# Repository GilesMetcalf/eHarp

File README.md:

# Lughnasadh eHarp
This is the ongoing eHarp project. 

## feature summary
The eharp is a full-featured MIDI controller that offers the following functions:
- Up to 32 notes that can be played
- Fully polyphonic
- A choice of 32 different scales (modes)
- A choice of MIDI channels
- Transposition from -6 to +6 intervals. Essentially any key in the octave.
- Selectable octave settings from -3 to +3
- 11 selectable velocity settings
- Pitch and Bend controls
- Sustain pedal input
- Multi-level menu system
- Save and Load up to 8 sets of parameters ("songs")
- Self-calibration to compensate for background light levels
- Several self-diagnostic features

## Architecture and principles
The eHarp is based on a scanned matrix of small lasers to detect an interruption to the beam (by sticking fingers into the beam!). The interruption is detected by a phototransistor which feeds an baseline-compensated analogue level amplifier and a digital comparator. A microcontroller (a Raspberry Pi Pico 2) runs CircuitPython code to detect the interruption, identify which laser is on at the time, makes appropriate adjustments depending on the selected scale, velocity, bend value and transposition, and them emits MIDI messages to whatever device is on the end. 

The lasers are small 5mW diodes (such as are used in laser pointers), scanned sequentially by the microcontroller. Only "active" diodes are scanned, so any which are not part of the scale, or that have been identified as blocked or faulty by the calibration routines are not illuminated and are skipped from the scan. This reduces any latency in generating notes, as well as preventing spurious notes playing.

## Boot and run sequences
### Boot up and calibration
On initially powering the eHarp up, the (numerous) I/O ports are initialised and the baseline offset output set to a default value of approximately 150mV. A flag is set to prevent any MIDI output (this stops random notes playing during calibration). A nice splash screen is displayed for a few seconds. This serves no purpose other than being flash, and can be aborted by pressing any button on the menu panel. The software twiddles it's little digital thumbs while this is displayed.
Once the splash expires, the eHarp drops into it's automated calibration routine. There are two elements to this. Firstly the baseline offset is adjusted to allow for the current ambient light by reading the sensor output (post amplification) with no lasers on. The offset voltage is adjusted to approximately 30-50mV above zero to give a bit of stability. 
Following the offset adjustment, all the lasers are scanned to check that they are producing an output and that the sensor is detecting them. (This assumes that there are no fingers in the way for this part!) Any which fail for any reason (poor and failing output - always a danger with cheap laser diodes! - misalignments or blockages, etc.) are marked as inactive and removed from normal scans. 
Finally, the main menu is displayed and the main scan routines are initiated.

### Run cycle
The run cycle essentially runs forever, and consists of three elements:
- The menu buttons are scanned. If any have been pressed, the menu subsystem executes whatever menu option is selected. This might be to change to a submenu, reset a state value (such as scale or key), or execute a calibration or diagnostic function. Once the action has been carried out, the menu returns to the parent level (or the main level, depending where it is in the heirarchy), and normal scanning continues.
- The laser matrix is scanned. All the available cells (0 to 31) are processed in sequence, and for each cell if the selected scale array and active note array both indicate that the cell is valid, the laser is illuminated. The sensor input is read, and if the beam is interrupted the current MIDI state for that note is checked. There are several possible outcomes at this stage:
  - The beam is not interrupted and the note is not active; do nothing and move on to the next cell.
  - The beam is not interrupted but the note was active; emit a <samp>NoteOff</samp> MIDI message.
  - The beam is interrupted and the note was active; do nothing and move on to the next cell.
  - The beam is interrupted and the note was not active; emit a <samp>NoteOn</samp> MIDI message.
- Once the cell has been  processed, the laser is turned off and the sequence moves to the next cell.
- Finally, once all the cells have been processed, the MIDI state (bend/mod controls and octave selection buttons) are scanned. Any changes are detected and state variables set accordingly. The bend and mod controls are analogue inputs from a joystick and are captured using the Pico's built-in ADC.

### MIDI generation
For each MIDI note generation event, before the <samp>NoteOn</samp> event is emitted, some adjustments and enhancements are needed. The <samp>NoteOn</samp> event contains several parameters:
- The actual note number, which is calculated from the cell number (0 to 31) plus the MIDI offset to get to the actual note (C3 for the bottom note). This is then appended with the transposition value (-6 to +6) and the octave value to give the required note.
- The velocity value (how hard the 'key' has been struck). This comes from the selected velocity value
- The MIDI channel number. This comes from the selected channel value.
  
On top of that, there are some MIDI control events that also need to be emitted, although these are not directly associated with a specific note:
- If the Bend control value has changed, a <samp>PitchBend</samp> event is emitted.
- If the Mod control value has changed, a <samp>ControlChange(1)</samp> event is emitted.
- If the Sustain pedal is pressed, a <samp>ControlChange(64)</samp> event is emitted with a parameter of 127 (sustain on).
- If the Sustain pedal is released, a <samp>ControlChange(64)</samp> event is emitted with a parameter of 0 (sustain off).

### Parameter saving
The user can save and reload up to 8 sets of parameters for different songs:
- Scale
- Velocity
- MIDI channel
- Transposition
- Octave setting

*My thanks also to Adam Metcalf for the original inspiration, as well as much sage advice during the design and build of this project (and not laughing at my terrible electronics!)*

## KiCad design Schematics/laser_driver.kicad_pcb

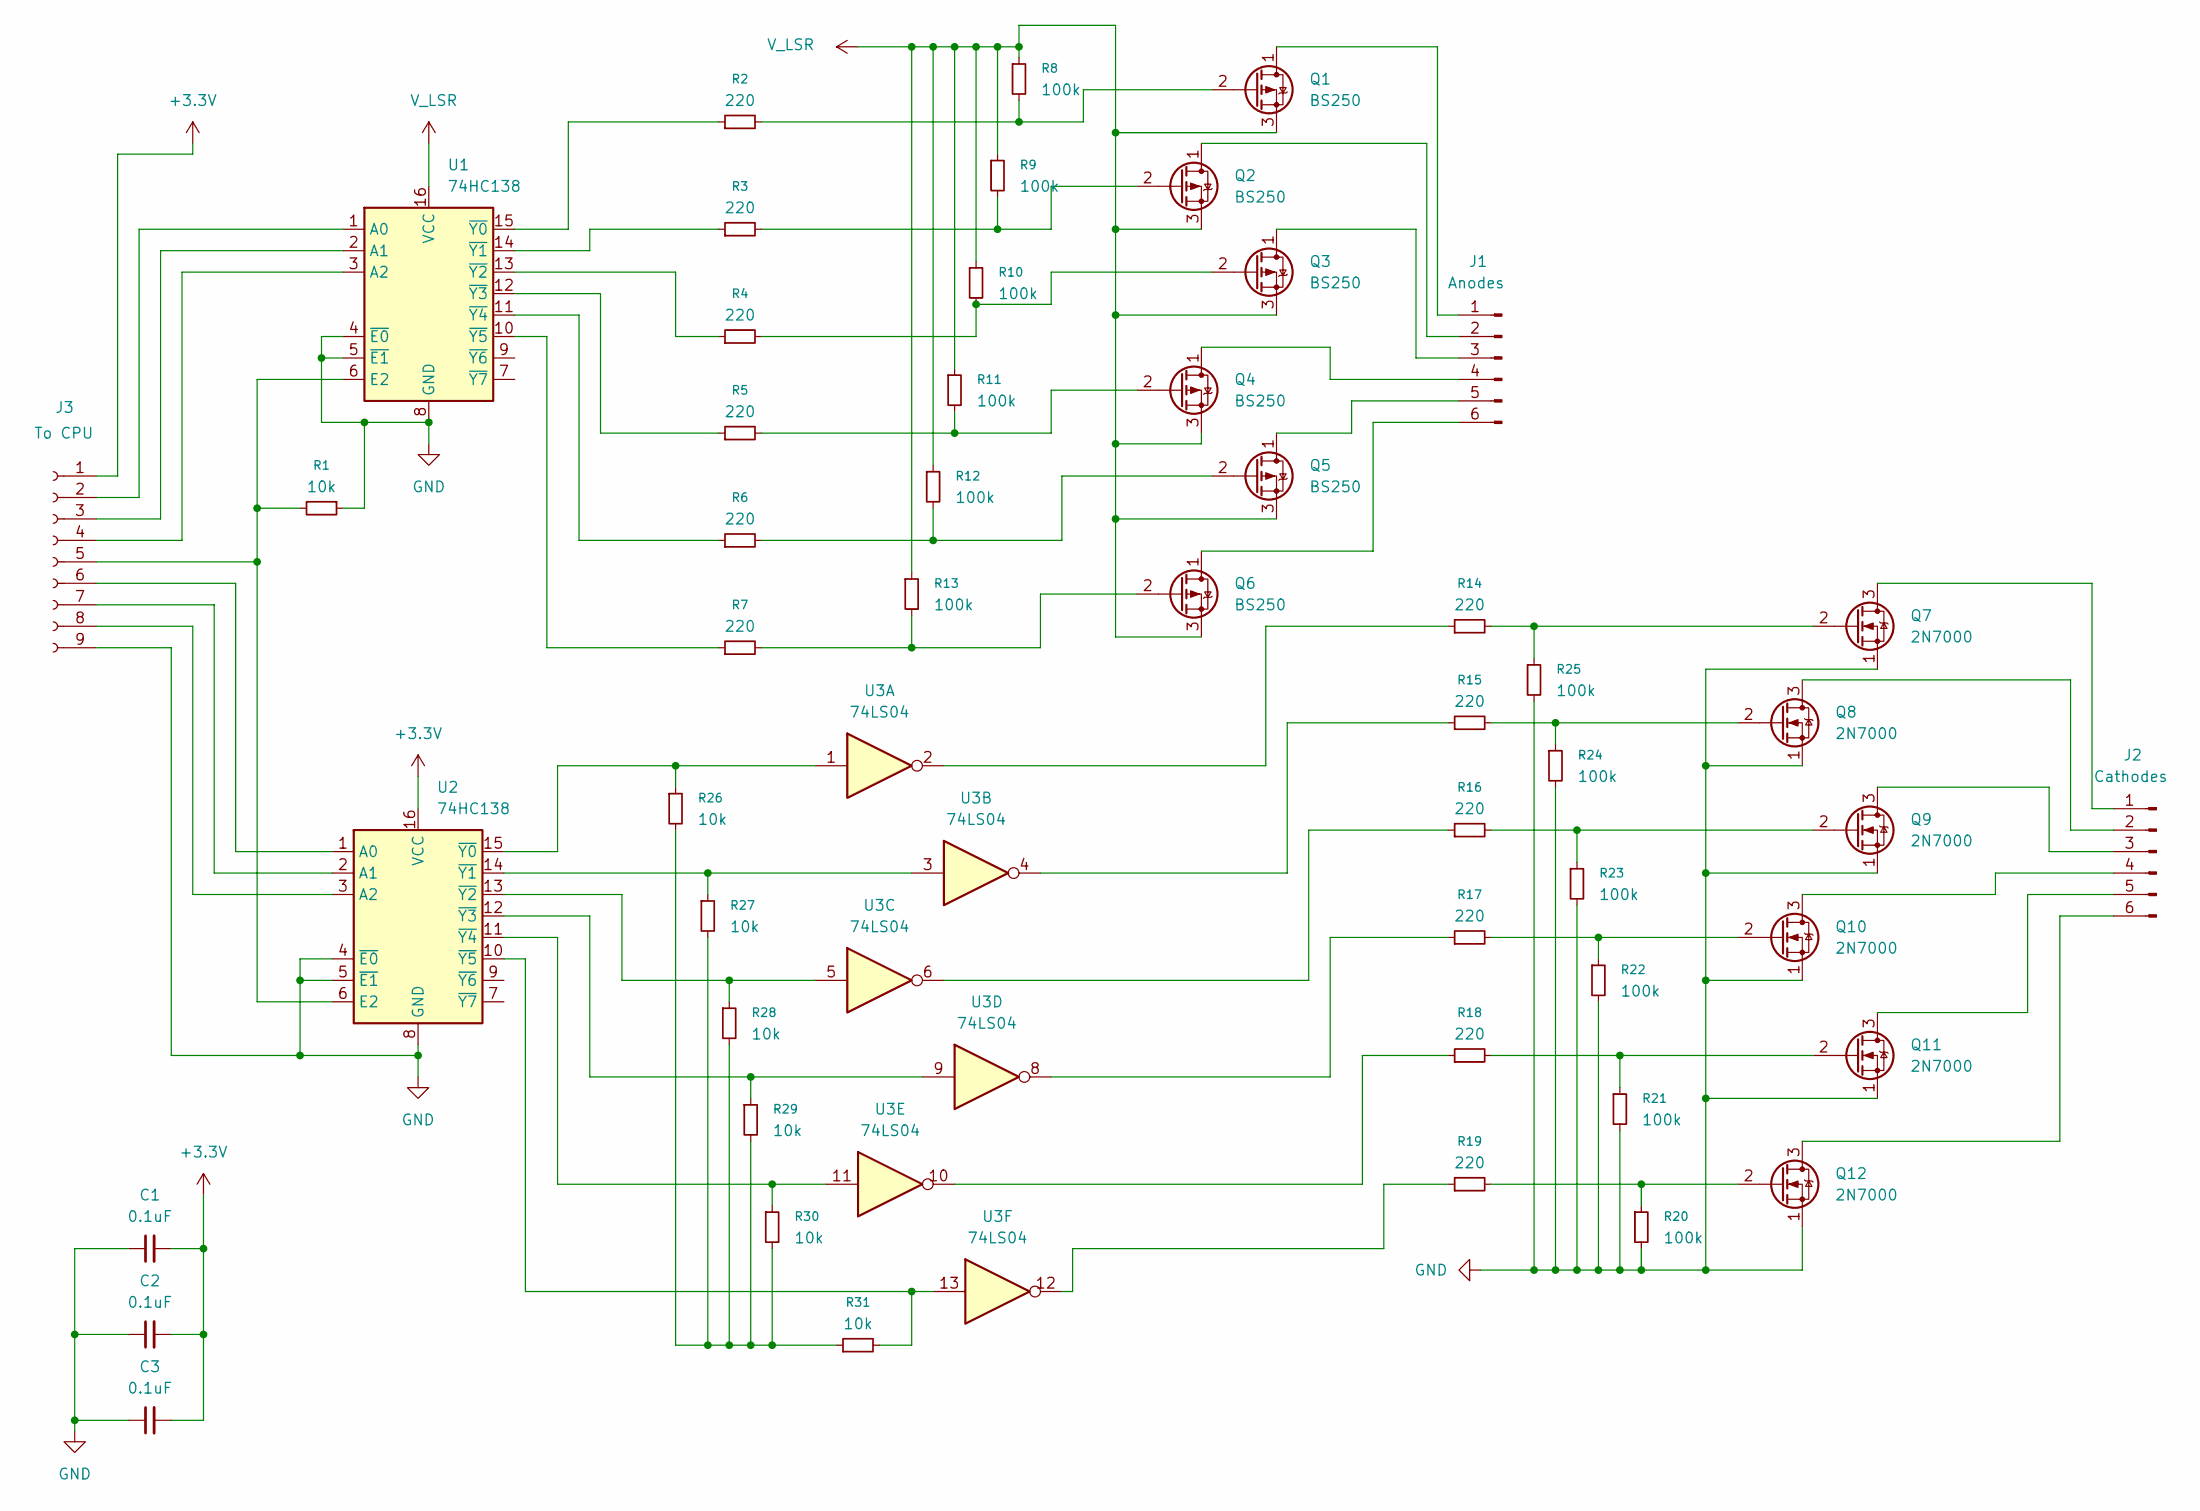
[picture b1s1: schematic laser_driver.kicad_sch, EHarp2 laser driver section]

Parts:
C1, C2, C3: 0.1uF; C_Rect_L10.0mm_W3.0mm_P7.50mm_FKS3_FKP3
J1: Anodes; PinHeader_1x06_P2.54mm_Vertical
J2: Cathodes; PinHeader_1x06_P2.54mm_Vertical
J3: To CPU; PinHeader_1x09_P2.54mm_Vertical
Q1, Q2, Q3, Q4, Q5, Q6: BS250; TO-92_Inline
Q7, Q8, Q9, Q10, Q11, Q12: 2N7000; TO-92_Inline
R1, R26, R27, R28, R29, R30, R31: 10k; R_Axial_DIN0204_L3.6mm_D1.6mm_P7.62mm_Horizontal
R2, R3, R4, R5, R6, R7, R14, R15, R16, R17, R18, R19: 220; R_Axial_DIN0204_L3.6mm_D1.6mm_P7.62mm_Horizontal
R8, R9, R10, R11, R12, R13, R20, R21, R22, R23, R24, R25: 100k; R_Axial_DIN0204_L3.6mm_D1.6mm_P7.62mm_Horizontal
U1, U2: 74HC138; DIP-16_W10.16mm
U3: 74LS04

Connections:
+3.3V: C1.2, C2.2, C3.2, J3.1, U2.16 (VCC)
GND: C1.1, C2.1, C3.1, J3.9, Q7.1 (S), Q8.1 (S), Q9.1 (S), Q10.1 (S), Q11.1 (S), Q12.1 (S), R1.1, R20.2, R21.2, R22.2, R23.2, R24.2, R25.2, U1.4 (~E0), U1.5 (~E1), U1.8 (GND), U2.4 (~E0), U2.5 (~E1), U2.8 (GND)
unnamed: J1.1, Q1.1 (D)
unnamed: J1.2, Q2.1 (D)
unnamed: J1.3, Q3.1 (D)
unnamed: J1.4, Q4.1 (D)
unnamed: J1.5, Q5.1 (D)
unnamed: J1.6, Q6.1 (D)
unnamed: J2.1, Q7.3 (D)
unnamed: J2.2, Q8.3 (D)
unnamed: J2.3, Q9.3 (D)
unnamed: J2.4, Q10.3 (D)
unnamed: J2.5, Q11.3 (D)
unnamed: J2.6, Q12.3 (D)
unnamed: J3.2, U1.1 (A0)
unnamed: J3.3, U1.2 (A1)
unnamed: J3.4, U1.3 (A2)
unnamed: J3.5, R1.2, U1.6 (E2), U2.6 (E2)
unnamed: J3.6, U2.1 (A0)
unnamed: J3.7, U2.2 (A1)
unnamed: J3.8, U2.3 (A2)
unnamed: Q1.2 (G), R2.2, R8.2
unnamed: Q2.2 (G), R3.2, R9.2
unnamed: Q3.2 (G), R4.2, R10.2
unnamed: Q4.2 (G), R5.2, R11.2
unnamed: Q5.2 (G), R6.2, R12.2
unnamed: Q6.2 (G), R7.2, R13.2
unnamed: Q7.2 (G), R14.2, R25.1
unnamed: Q8.2 (G), R15.2, R24.1
unnamed: Q9.2 (G), R16.2, R23.1
unnamed: Q10.2 (G), R17.2, R22.1
unnamed: Q11.2 (G), R18.2, R21.1
unnamed: Q12.2 (G), R19.2, R20.1
unnamed: R14.1, U3.2
unnamed: R15.1, U3.4
unnamed: R16.1, U3.6
unnamed: R17.1, U3.8
unnamed: R18.1, U3.10
unnamed: R19.1, U3.12
unnamed: R26.2, R27.2, R28.2, R29.2, R30.2, R31.1
unnamed: R2.1, U1.15 (~Y0)
unnamed: R3.1, U1.14 (~Y1)
unnamed: R4.1, U1.13 (~Y2)
unnamed: R5.1, U1.12 (~Y3)
unnamed: R6.1, U1.11 (~Y4)
unnamed: R7.1, U1.10 (~Y5)
unnamed: R26.1, U2.15 (~Y0), U3.1
unnamed: R27.1, U2.14 (~Y1), U3.3
unnamed: R28.1, U2.13 (~Y2), U3.5
unnamed: R29.1, U2.12 (~Y3), U3.9
unnamed: R30.1, U2.11 (~Y4), U3.11
unnamed: R31.2, U2.10 (~Y5), U3.13
V_LSR: Q1.3 (S), Q2.3 (S), Q3.3 (S), Q4.3 (S), Q5.3 (S), Q6.3 (S), R8.1, R9.1, R10.1, R11.1, R12.1, R13.1, U1.16 (VCC)

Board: 2 copper layers, 52 parts (0 on the bottom side), 53 nets, no tracks yet.

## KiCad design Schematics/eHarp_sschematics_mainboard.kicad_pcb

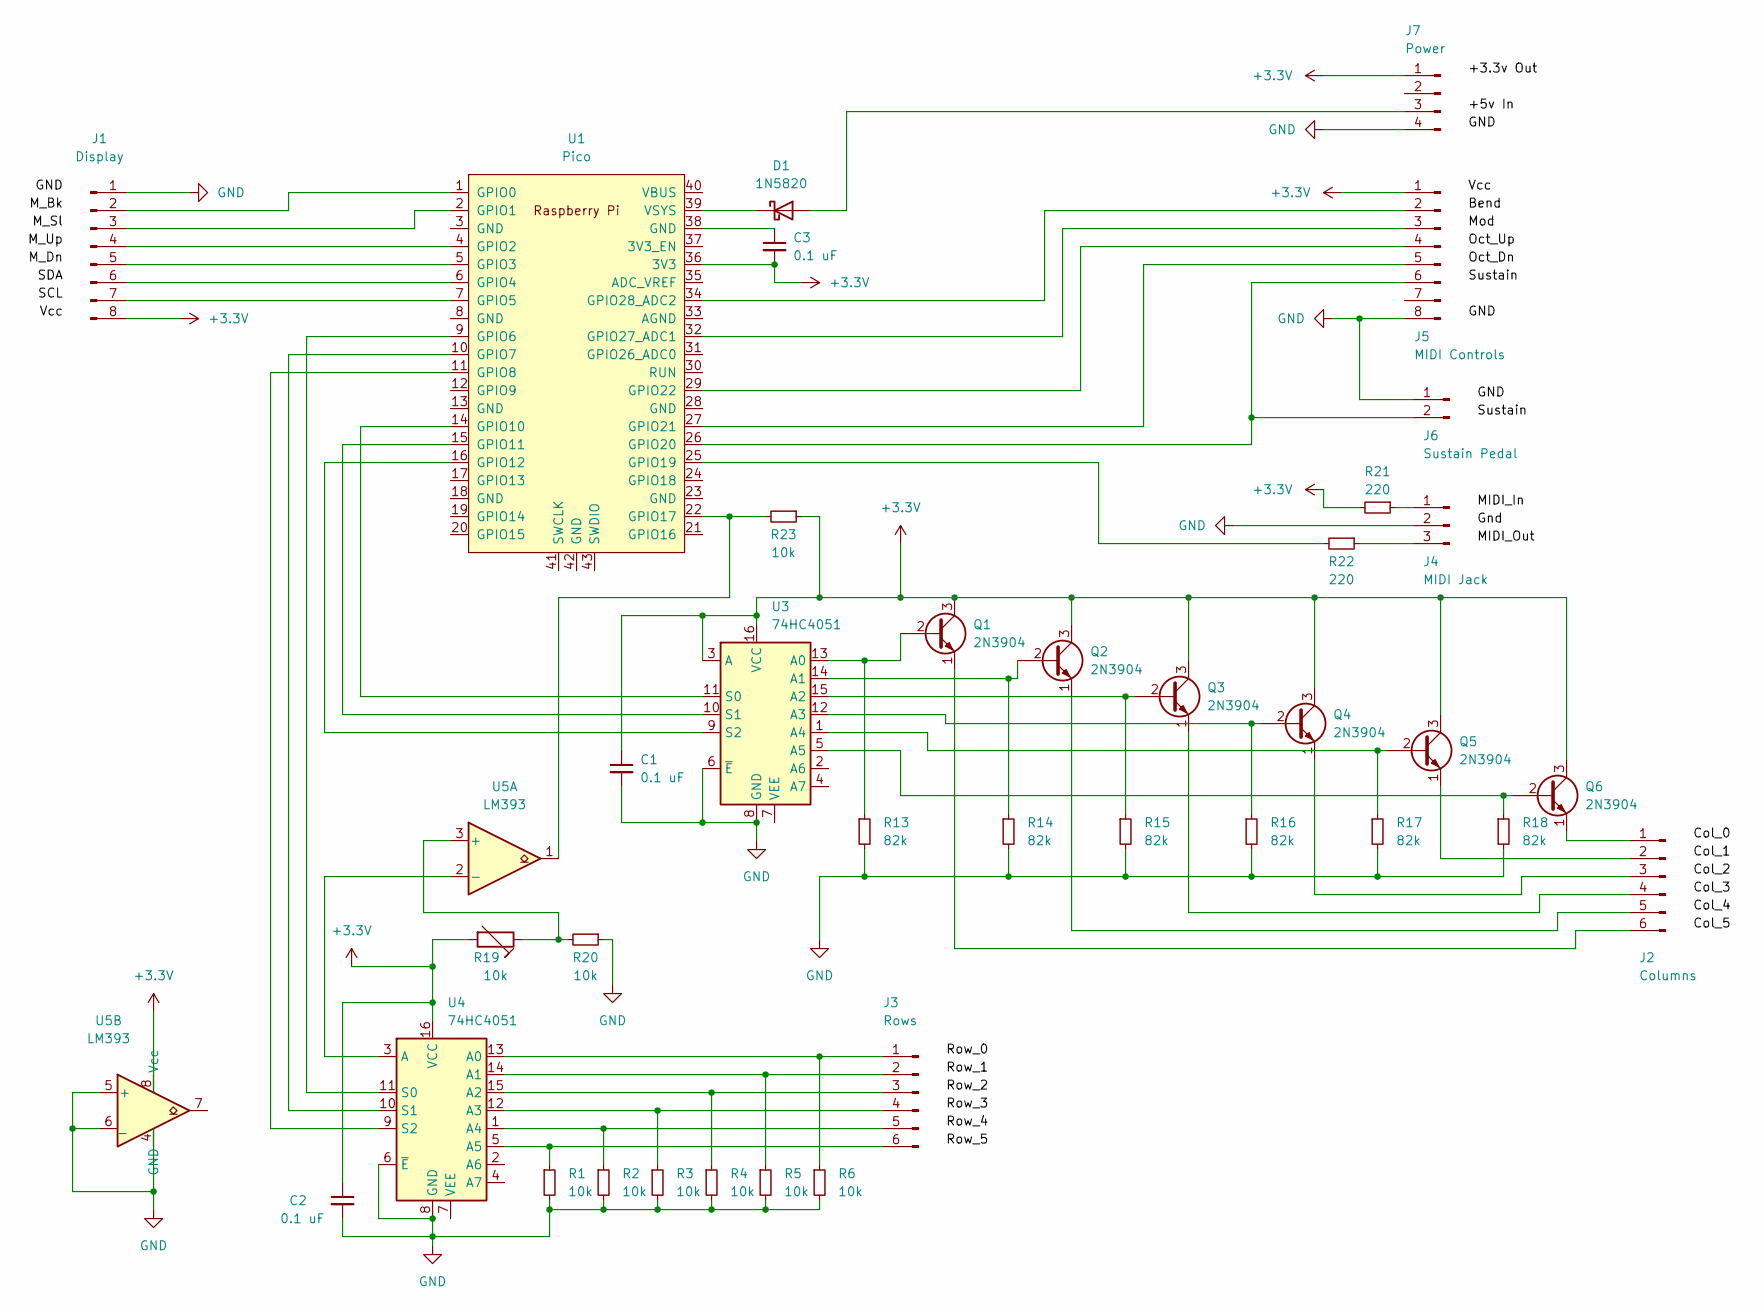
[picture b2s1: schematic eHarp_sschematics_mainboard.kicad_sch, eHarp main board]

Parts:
C1, C2, C3: 0.1 uF; C_Rect_L9.0mm_W2.5mm_P7.50mm_MKT
D1: 1N5820; D_DO-15_P10.16mm_Horizontal
J1: Display; PinHeader_1x08_P2.54mm_Vertical
J2: Columns; PinHeader_1x06_P2.54mm_Vertical
J3: Rows; PinHeader_1x06_P2.54mm_Vertical
J4: MIDI Jack; PinHeader_1x03_P2.54mm_Vertical
J5: MIDI Controls; PinHeader_1x08_P2.54mm_Vertical
J6: Sustain Pedal; PinHeader_1x02_P2.54mm_Vertical
J7: Power; PinHeader_1x04_P2.54mm_Vertical
Q1, Q2, Q3, Q4, Q5, Q6: 2N3904; TO-92_Inline
R1, R2, R3, R4, R5, R6, R20, R23: 10k; R_Axial_DIN0204_L3.6mm_D1.6mm_P7.62mm_Horizontal
R13, R14, R15, R16, R17, R18: 82k; R_Axial_DIN0204_L3.6mm_D1.6mm_P7.62mm_Horizontal
R19: 10k; Potentiometer_Bourns_3266W_Vertical
R21, R22: 220; R_Axial_DIN0204_L3.6mm_D1.6mm_P7.62mm_Horizontal
U1: Pico; DIP-40_W25.4mm_Socket
U3, U4: 74HC4051; DIP-16_W7.62mm
U5: LM393; DIP-8_W7.62mm

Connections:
+3V3: C1.1, C2.1, C3.2, J1.8, J5.1, J7.1, Q1.3 (C), Q2.3 (C), Q3.3 (C), Q4.3 (C), Q5.3 (C), Q6.3 (C), R19.2, R21.2, R23.1, U1.36 (3V3), U3.3 (A), U3.16 (VCC), U4.16 (VCC), U5.8 (Vcc)
GND: C1.2, C2.2, J1.1, J4.2, J5.8, J6.1, J7.4, R1.2, R2.2, R3.2, R4.2, R5.2, R6.2, R13.2, R14.2, R15.2, R16.2, R17.2, R18.2, R20.1, U3.6 (~E), U3.8 (GND), U4.6 (~E), U4.8 (GND), U5.4 (GND), U5.5 (+), U5.6 (_)
unnamed: C3.1, U1.38 (GND)
unnamed: D1.1 (K), U1.39 (VSYS)
unnamed: D1.2 (A), J7.3
unnamed: J1.2, U1.1 (GPIO0)
unnamed: J1.3, U1.2 (GPIO1)
unnamed: J1.4, U1.4 (GPIO2)
unnamed: J1.5, U1.5 (GPIO3)
unnamed: J1.6, U1.6 (GPIO4)
unnamed: J1.7, U1.7 (GPIO5)
unnamed: J2.1, Q6.1 (E)
unnamed: J2.2, Q5.1 (E)
unnamed: J2.3, Q4.1 (E)
unnamed: J2.4, Q3.1 (E)
unnamed: J2.5, Q2.1 (E)
unnamed: J2.6, Q1.1 (E)
unnamed: J3.1, R6.1, U4.13 (A0)
unnamed: J3.2, R5.1, U4.14 (A1)
unnamed: J3.3, R4.1, U4.15 (A2)
unnamed: J3.4, R3.1, U4.12 (A3)
unnamed: J3.5, R2.1, U4.1 (A4)
unnamed: J3.6, R1.1, U4.5 (A5)
unnamed: J4.1, R21.1
unnamed: J4.3, R22.1
unnamed: J5.2, U1.34 (GPIO28_ADC2)
unnamed: J5.3, U1.32 (GPIO27_ADC1)
unnamed: J5.4, U1.29 (GPIO22)
unnamed: J5.5, U1.27 (GPIO21)
unnamed: J5.6, J6.2, U1.26 (GPIO20)
unnamed: Q1.2 (B), R13.1, U3.13 (A0)
unnamed: Q2.2 (B), R14.1, U3.14 (A1)
unnamed: Q3.2 (B), R15.1, U3.15 (A2)
unnamed: Q4.2 (B), R16.1, U3.12 (A3)
unnamed: Q5.2 (B), R17.1, U3.1 (A4)
unnamed: Q6.2 (B), R18.1, U3.5 (A5)
unnamed: R19.1, R20.2, U5.3 (+)
unnamed: R22.2, U1.25 (GPIO19)
unnamed: R23.2, U1.22 (GPIO17), U5.1
unnamed: U1.9 (GPIO6), U4.11 (S0)
unnamed: U1.10 (GPIO7), U4.10 (S1)
unnamed: U1.11 (GPIO8), U4.9 (S2)
unnamed: U1.14 (GPIO10), U3.11 (S0)
unnamed: U1.15 (GPIO11), U3.10 (S1)
unnamed: U1.16 (GPIO12), U3.9 (S2)
unnamed: U4.3 (A), U5.2 (-)

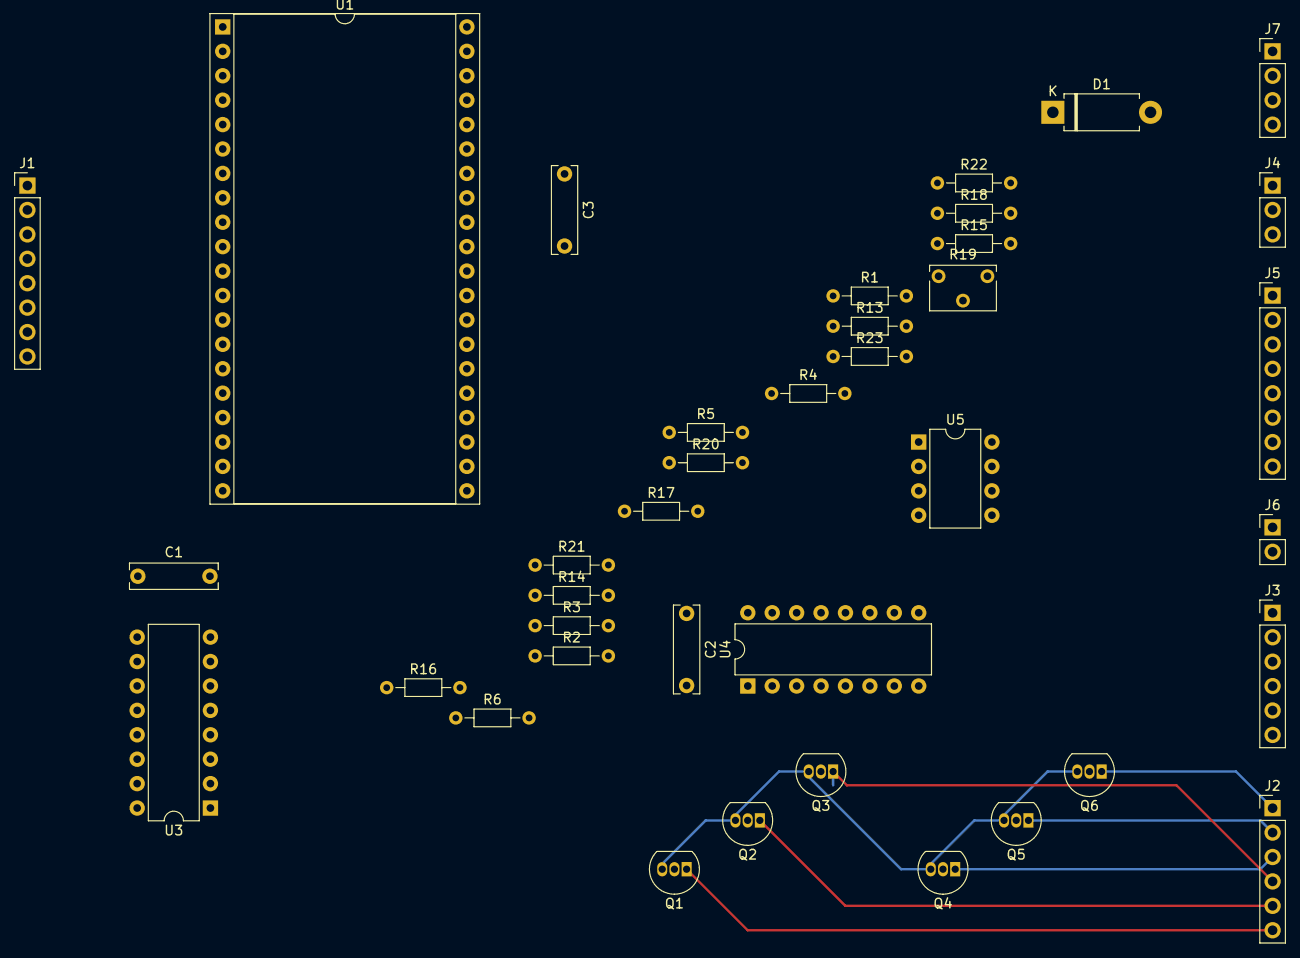
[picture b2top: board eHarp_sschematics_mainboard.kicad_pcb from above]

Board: 2 copper layers, 38 parts (0 on the bottom side), 46 nets.

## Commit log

2025-03-16 Initial commit - no code yet!
2025-03-17 Display and menus kinda working
2025-03-17 Midi stuff in place (not yet tested)
2025-03-21 Fully working! Yay!
2025-03-26 Set row and column parameters correctly
2025-03-26 Changes row and column ranges to 1-based
2025-03-26 Small change to claculate notes correctly
2025-08-02 Added test for dead LDRs
2026-04-18 Baseline implementation
2026-06-16 Lopts and lots of changes for new body and circuitry
2026-06-17 Updates for variable numbers of lasers. Removed redundant commented code. Addded scan test code
2026-06-17 Corrected laser_enable placing
2026-06-18 update splashscreen. Added some spaces for clarity.
2026-06-18 fixed some display issues with splashscreen, and added "press any button" capability to exit splash.
2026-06-19 Added single step function. Consolidated cell selection and laser control into one function.
2026-06-24 New menu system; new code for baseline management, updated schematics
2026-06-24 Small update to preset basline outout on boot.
2026-06-24 Create README.md
    Created README
2026-06-28 Added pullup for scan input. Externailsed constants to config.py
2026-06-28 Added schematics PDF
2026-06-29 General cleanup and added some design files
2026-06-29 Added user guide
2026-06-30 Removed KiCAD backup folder from repo
2026-06-30 Added save and load options. Global state variables condensed into a DICT. Added boot.py to allow file saves.
2026-06-30 Oops. should have been committed too.
